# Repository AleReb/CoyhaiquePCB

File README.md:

# ESP32 + SIM7600 Sensor Board (Coyhaique)

## Descripción del Proyecto

Este repositorio contiene los archivos de diseño de hardware (esquemáticos y placa PCB) diseñados en Autodesk EAGLE para una tarjeta basada en el microcontrolador **ESP32** integrada con el módulo de comunicación **SIM7600**. 

El propósito de esta placa es facilitar la conexión y adquisición de datos de múltiples sensores.

## Características Principales

* **Microcontrolador:** ESP32 (Wi-Fi y Bluetooth integrados).
* **Comunicación Móvil:** Módulo SIM7600 (soporte para 4G/LTE, GPS, etc.).
* **Integración de Sensores:** Diseñado para agregar y leer diversos sensores a través de sus pines de expansión y borneras.
* **Diseño CAD:** Archivos de diseño creados en EAGLE (`.sch`, `.brd` y archivos de fabricación CAM `.job`).

## Contenido del Repositorio

* `Board_760032.sch` / `Board_7600.sch`: Esquemáticos del diseño del circuito.
* `Board_760032.brd` / `Board_7600.brd`: Diseño de la placa de circuito impreso (PCB).
* `*.job`: Archivos en formato CAM Job de EAGLE para la generación de archivos base de manufactura (Archivos Gerber, Taladros, etc).
* Otros respaldos y librerías generadas por la herramienta.

## Autor

**Alejandro Rebolledo**  
* Correo electrónico: [arebolledo@udd.cl](mailto:arebolledo@udd.cl)

## Descargo de Responsabilidad / Disclaimer

Este proyecto y todo el material incluido (código, esquemáticos, diseños de placa PCB y cualquier otra documentación) se proporcionan **"tal cual" ("as is")**, sin garantías de ningún tipo, ya sean expresas o implícitas. Esto incluye, pero no se limita a, las garantías de comerciabilidad, idoneidad para un propósito particular y no infracción. 

El código se ofrece y el usuario utiliza estos diseños o fabricaciones derivadas enteramente **bajo su propio riesgo**. El autor no se hace responsable por ningún daño directo, indirecto, incidental, especial, ejemplar o consecuente (incluyendo la pérdida de datos, daños a equipos u otros daños) que surjan de alguna forma del uso de este proyecto. Asegúrese de revisar minuciosamente y validar los componentes, valores, polaridades y esquemáticos antes de la manufactura o su puesta en marcha.

## Licencia

Este proyecto se distribuye bajo la licencia **Creative Commons Attribution-NonCommercial 4.0 International (CC BY-NC 4.0)**. 
Puede consultar el texto completo de la licencia en el archivo [LICENSE](LICENSE) incluido en este repositorio o visitar [Creative Commons CC BY-NC 4.0](https://creativecommons.org/licenses/by-nc/4.0/).

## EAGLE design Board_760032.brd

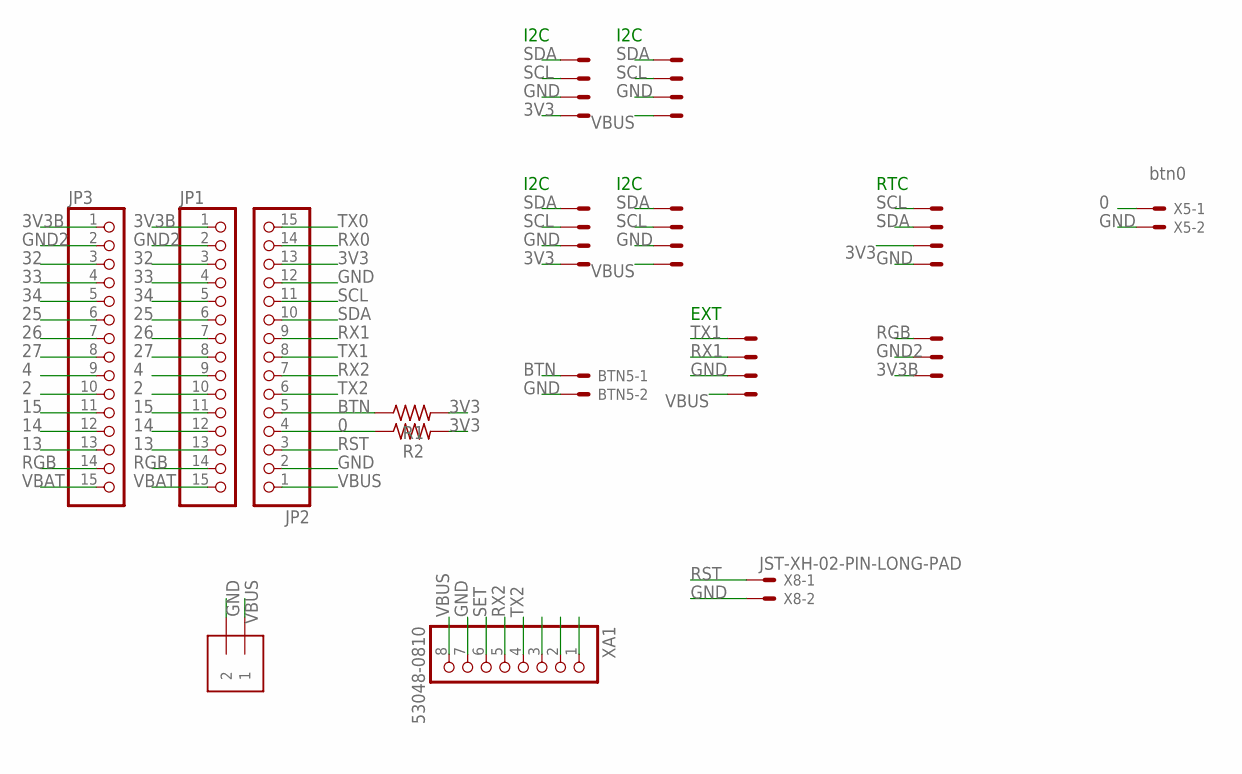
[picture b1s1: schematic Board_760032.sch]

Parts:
BTN5: JST-XH-02-PIN-LONG-PAD; JST-XH-02-PACKAGE-LONG-PAD
J1: 1X2-3.5MM
JP1, JP2, JP3: PINHD-1X15; 1X15
R1, R2: R-US_0207/7; 0207/7
RTC: JST-XH-04-PIN-LONG-PAD; JST-XH-04-PACKAGE-LONG-PAD
X1, X2, X3, X6, X9: JST-XH-04-PIN-LONG-PAD; JST-XH-04-PACKAGE-LONG-PAD
X4: JST-XH-03-PIN-LONG-PAD; JST-XH-03-PACKAGE-LONG-PAD
X5: btn0; JST-XH-02-PACKAGE-LONG-PAD
X8: JST-XH-02-PIN-LONG-PAD; JST-XH-02-PACKAGE-LONG-PAD
XA1: 53048-0810; MOLEX_53048-0810

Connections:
0: JP2.4, R2.1, X5.1
2: JP1.10, JP3.10
3V3: JP2.13, R1.2, R2.2, RTC.3, X1.4, X3.4
3V3B: JP1.1, JP3.1, X4.3
4: JP1.9, JP3.9
13: JP1.13, JP3.13
14: JP1.12, JP3.12
15: JP1.11, JP3.11
25: JP1.6, JP3.6
26: JP1.7, JP3.7
27: JP1.8, JP3.8
32: JP1.3, JP3.3
33: JP1.4, JP3.4
34: JP1.5, JP3.5
BTN: BTN5.1, JP2.5, R1.1
GND: BTN5.2, J1.2, JP2.2, JP2.12, RTC.4, X1.3, X2.3, X3.3, X5.2, X6.3, X8.2, X9.3, XA1.7
GND2: JP1.2, JP3.2, X4.2
RGB: JP1.14, JP3.14, X4.1
RST: JP2.3, X8.1
RX0: JP2.14
RX1: JP2.9, X6.2
RX2: JP2.7, XA1.5
SCL: JP2.11, RTC.1, X1.2, X2.2, X3.2, X9.2
SDA: JP2.10, RTC.2, X1.1, X2.1, X3.1, X9.1
SET: XA1.6
TX0: JP2.15
TX1: JP2.8, X6.1
TX2: JP2.6, XA1.4
VBAT: JP1.15, JP3.15
VBUS: J1.1, JP2.1, X2.4, X6.4, X9.4, XA1.8

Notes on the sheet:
RTC
I2C
EXT

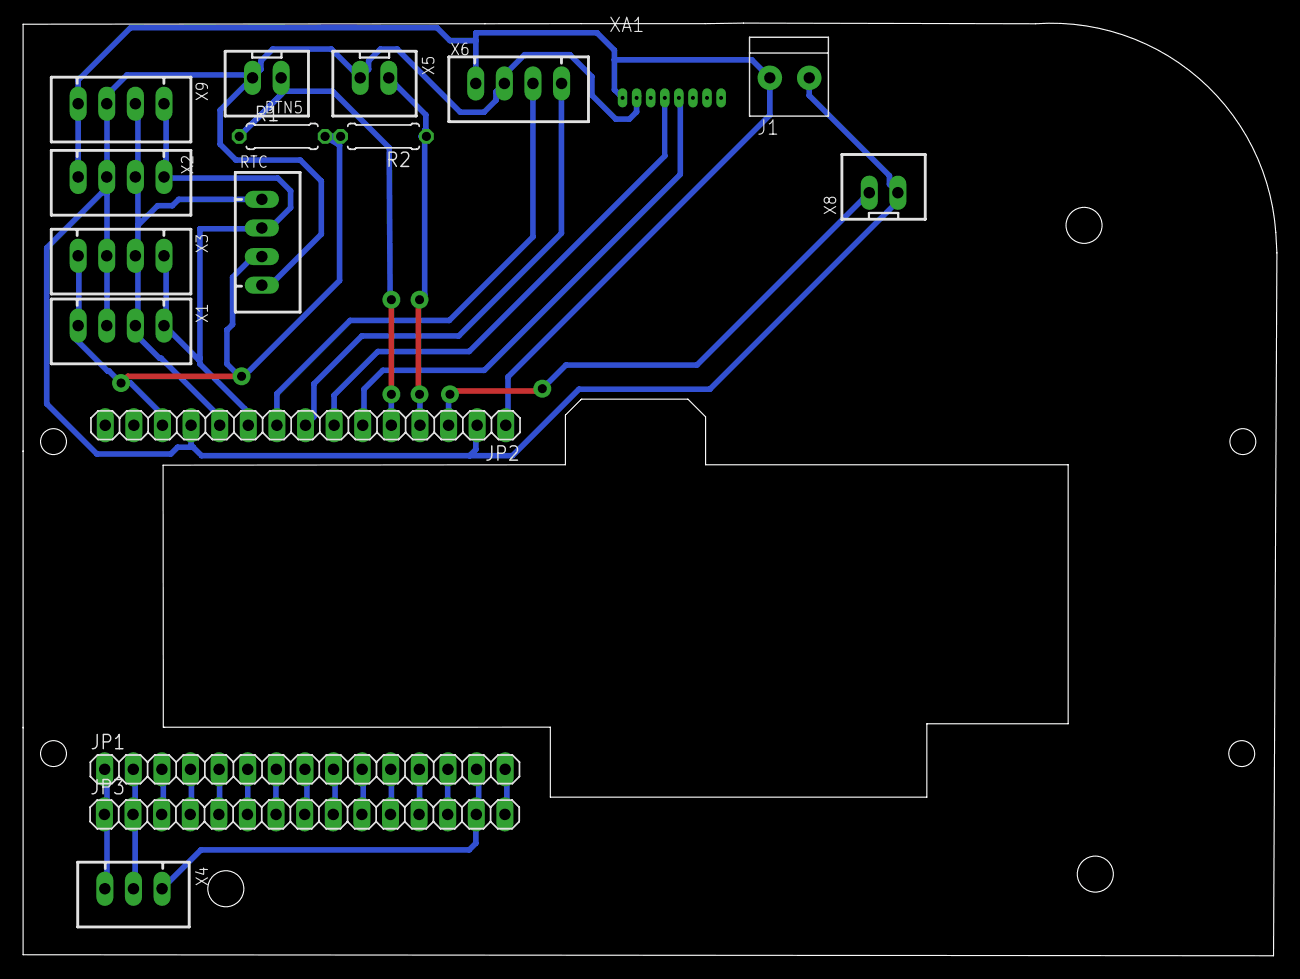
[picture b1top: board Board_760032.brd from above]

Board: 2 copper layers, 111.3 x 82.8 mm, 17 parts (0 on the bottom side), 27 nets.

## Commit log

2026-03-05 refactor: Update board design files to version 2.
2026-03-05 feat: Create new schematic file and remove `diy-modules` library from board layout.
2026-03-12 feat: Update schematic and board layout files.
